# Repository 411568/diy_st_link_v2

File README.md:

<h2>🧐 Features</h2>

ST-LINK is a programmer used with STM32 microcontrollers. It is sold by STMicroelectronics and by many other manufacturers and is included in a number of Nucleo/Discovery/etc. development boards.
Because of that, the schematics for it are available on the internet and you can build one yourself... and that is what I did.

My schematic was inspired by two diy projects, available under the following links: [STM32World](https://stm32world.com/wiki/DIY_STM32_Programmer_(ST-Link/V2-1)), [EmbdedBlog](https://embedblog.eu/?p=780). 
The design was then compared with one of STMs own designs from a Nucleo board.
You may think that the schematics could be easily reverse engineered, but you can't get the firmware for it, as it is proprietary STM softwa, right? Well, it seems someone has already done the job for us: [bootloader](https://github.com/Krakenw/Stlink-Bootloaders).

The schematic and PCB were both designed using KiCAD 6.0

<h2>💻 Parts list</h2>

* STM32F103C8T6 microcontroller (you can use the CBT6 for more memory)
* TC1263 3.3V linear regulator
* IDC connector
* pin header for programming
* USB B connector
* 2x 0805 SMD LED
* 2x 220Ohm resistor
* 2x 100Ohm resistor
* 1MOhm resistor
* 3x 10kOhm resistor
* 2x 100kOhm resistor
* 2x 4.7kOhm resistor
* 1.5kOhm resistor
* 36kOhm resistor
* 470pF ceramic capacitor
* 1uF electrolytic capacitor
* 4x 100nF ceramic capacitor
* 2x 20pF ceramic capacitor

<h2>📝 Assembled project</h2>

<h2>🛡️ License:</h2>

This project is licensed under the MIT License.

<h2> 🙋‍♂️Authors </h2>

- Krzysztof Sikora

<h2>💖Like my work?</h2>

If you have any questions about the project feel free to contact us via email: krzysieksikora717@gmail.com

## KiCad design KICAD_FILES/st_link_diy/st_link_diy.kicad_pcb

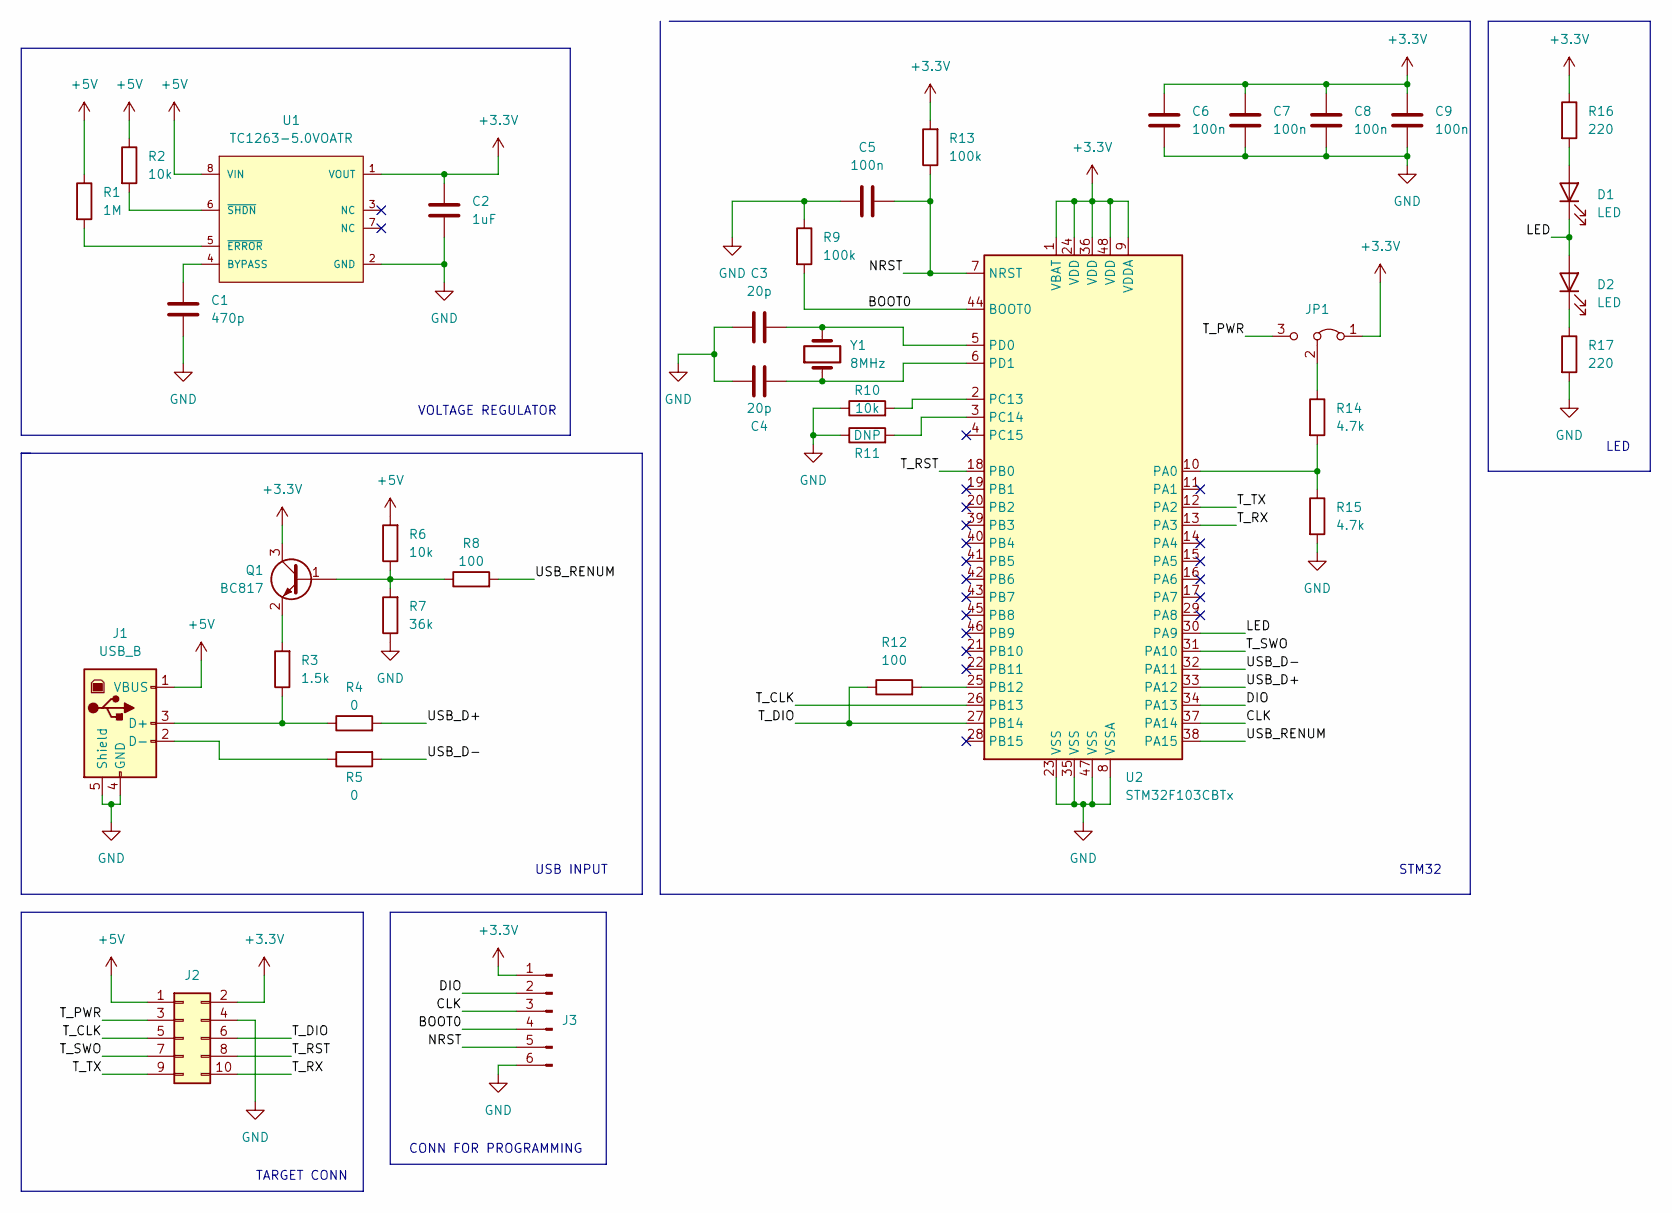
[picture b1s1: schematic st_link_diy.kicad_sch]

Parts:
C1: 470p; C_0805_2012Metric_Pad1.18x1.45mm_HandSolder
C2: 1uF; C_Elec_4x5.4
C3, C4: 20p; C_0603_1608Metric_Pad1.08x0.95mm_HandSolder
C5, C6, C7, C8, C9: 100n; C_0805_2012Metric_Pad1.18x1.45mm_HandSolder
D1, D2: LED; LED_0805_2012Metric_Pad1.15x1.40mm_HandSolder
J1: USB_B; USB_B_OST_USB-B1HSxx_Horizontal
J2: Conn_02x05_Odd_Even; IDC-Header_2x05_P2.54mm_Vertical
J3: Conn_01x06_Male; PinHeader_1x06_P2.54mm_Vertical
JP1: Jumper_3_Bridged12; PinHeader_1x03_P2.54mm_Vertical
Q1: BC817; SOT-23
R1: 1M; R_1206_3216Metric_Pad1.30x1.75mm_HandSolder
R2, R6, R10: 10k; R_1206_3216Metric_Pad1.30x1.75mm_HandSolder
R3: 1.5k; R_1206_3216Metric_Pad1.30x1.75mm_HandSolder
R4, R5: 0; R_1206_3216Metric_Pad1.30x1.75mm_HandSolder
R7: 36k; R_1206_3216Metric_Pad1.30x1.75mm_HandSolder
R8, R12: 100; R_1206_3216Metric_Pad1.30x1.75mm_HandSolder
R9, R13: 100k; R_1206_3216Metric_Pad1.30x1.75mm_HandSolder
R11: DNP; R_1206_3216Metric_Pad1.30x1.75mm_HandSolder
R14, R15: 4.7k; R_1206_3216Metric_Pad1.30x1.75mm_HandSolder
R16, R17: 220; R_1206_3216Metric_Pad1.30x1.75mm_HandSolder
U1: TC1263-5.0VOATR; SOIC-8-1EP_3.9x4.9mm_P1.27mm_EP2.29x3mm
U2: STM32F103CBTx; LQFP-48_7x7mm_P0.5mm
Y1: 8MHz; Crystal_SMD_HC49-SD_HandSoldering

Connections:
+3V3: C2.1, C6.1, C7.1, C8.1, C9.1, J2.2, J3.1, JP1.1 (A), Q1.3 (C), R13.2, R16.1, U1.1 (VOUT), U2.1 (VBAT), U2.9 (VDDA), U2.24 (VDD), U2.36 (VDD), U2.48 (VDD)
+5V: J1.1 (VBUS), J2.1, R1.1, R2.1, R6.2, U1.8 (VIN)
/BOOT0: J3.4, R9.2, U2.44 (BOOT0)
/CLK: J3.3, U2.37 (PA14)
/DIO: J3.2, U2.34 (PA13)
/LED: D1.1 (K), D2.2 (A), U2.30 (PA9)
/NRST: C5.2, J3.5, R13.1, U2.7 (NRST)
/T_CLK: J2.5, U2.26 (PB13)
/T_DIO: J2.6, R12.1, U2.27 (PB14)
/T_PWR: J2.3, JP1.3 (B)
/T_RST: J2.8, U2.18 (PB0)
/T_RX: J2.10, U2.13 (PA3)
/T_SWO: J2.7, U2.31 (PA10)
/T_TX: J2.9, U2.12 (PA2)
/USB_D+: R4.2, U2.33 (PA12)
/USB_D-: R5.2, U2.32 (PA11)
/USB_RENUM: R8.2, U2.38 (PA15)
GND: C1.2, C2.2, C3.2, C4.1, C5.1, C6.2, C7.2, C8.2, C9.2, J1.4 (GND), J1.5 (Shield), J2.4, J3.6, R7.1, R9.1, R10.1, R11.1, R15.2, R17.2, U1.2 (GND), U2.8 (VSSA), U2.23 (VSS), U2.35 (VSS), U2.47 (VSS)
unnamed: C1.1, U1.4 (BYPASS)
unnamed: C3.1, U2.5 (PD0), Y1.2
unnamed: C4.2, U2.6 (PD1), Y1.1
unnamed: D1.2 (A), R16.2
unnamed: D2.1 (K), R17.1
unnamed: J1.2 (D-), R5.1
unnamed: J1.3 (D+), R3.1, R4.1
unnamed: JP1.2 (C), R14.1
unnamed: Q1.1 (B), R6.1, R7.2, R8.1
unnamed: Q1.2 (E), R3.2
unnamed: R1.2, U1.5 (~ERROR)
unnamed: R2.2, U1.6 (~SHDN)
unnamed: R10.2, U2.2 (PC13)
unnamed: R11.2, U2.3 (PC14)
unnamed: R12.2, U2.25 (PB12)
unnamed: R14.2, R15.1, U2.10 (PA0)

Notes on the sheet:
STM32
TARGET CONN
VOLTAGE REGULATOR
USB INPUT
LED
CONN FOR PROGRAMMING

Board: 2 copper layers, 36 parts (0 on the bottom side), 34 nets, no tracks yet.

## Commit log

2023-02-27 added schematic v0.1
2023-02-27 finished schematic
2023-02-27 added pcb
2023-02-28 added pcb panel and gerbers
2023-03-01 added readme
2023-03-20 bootloader bin
2025-01-30 added images
